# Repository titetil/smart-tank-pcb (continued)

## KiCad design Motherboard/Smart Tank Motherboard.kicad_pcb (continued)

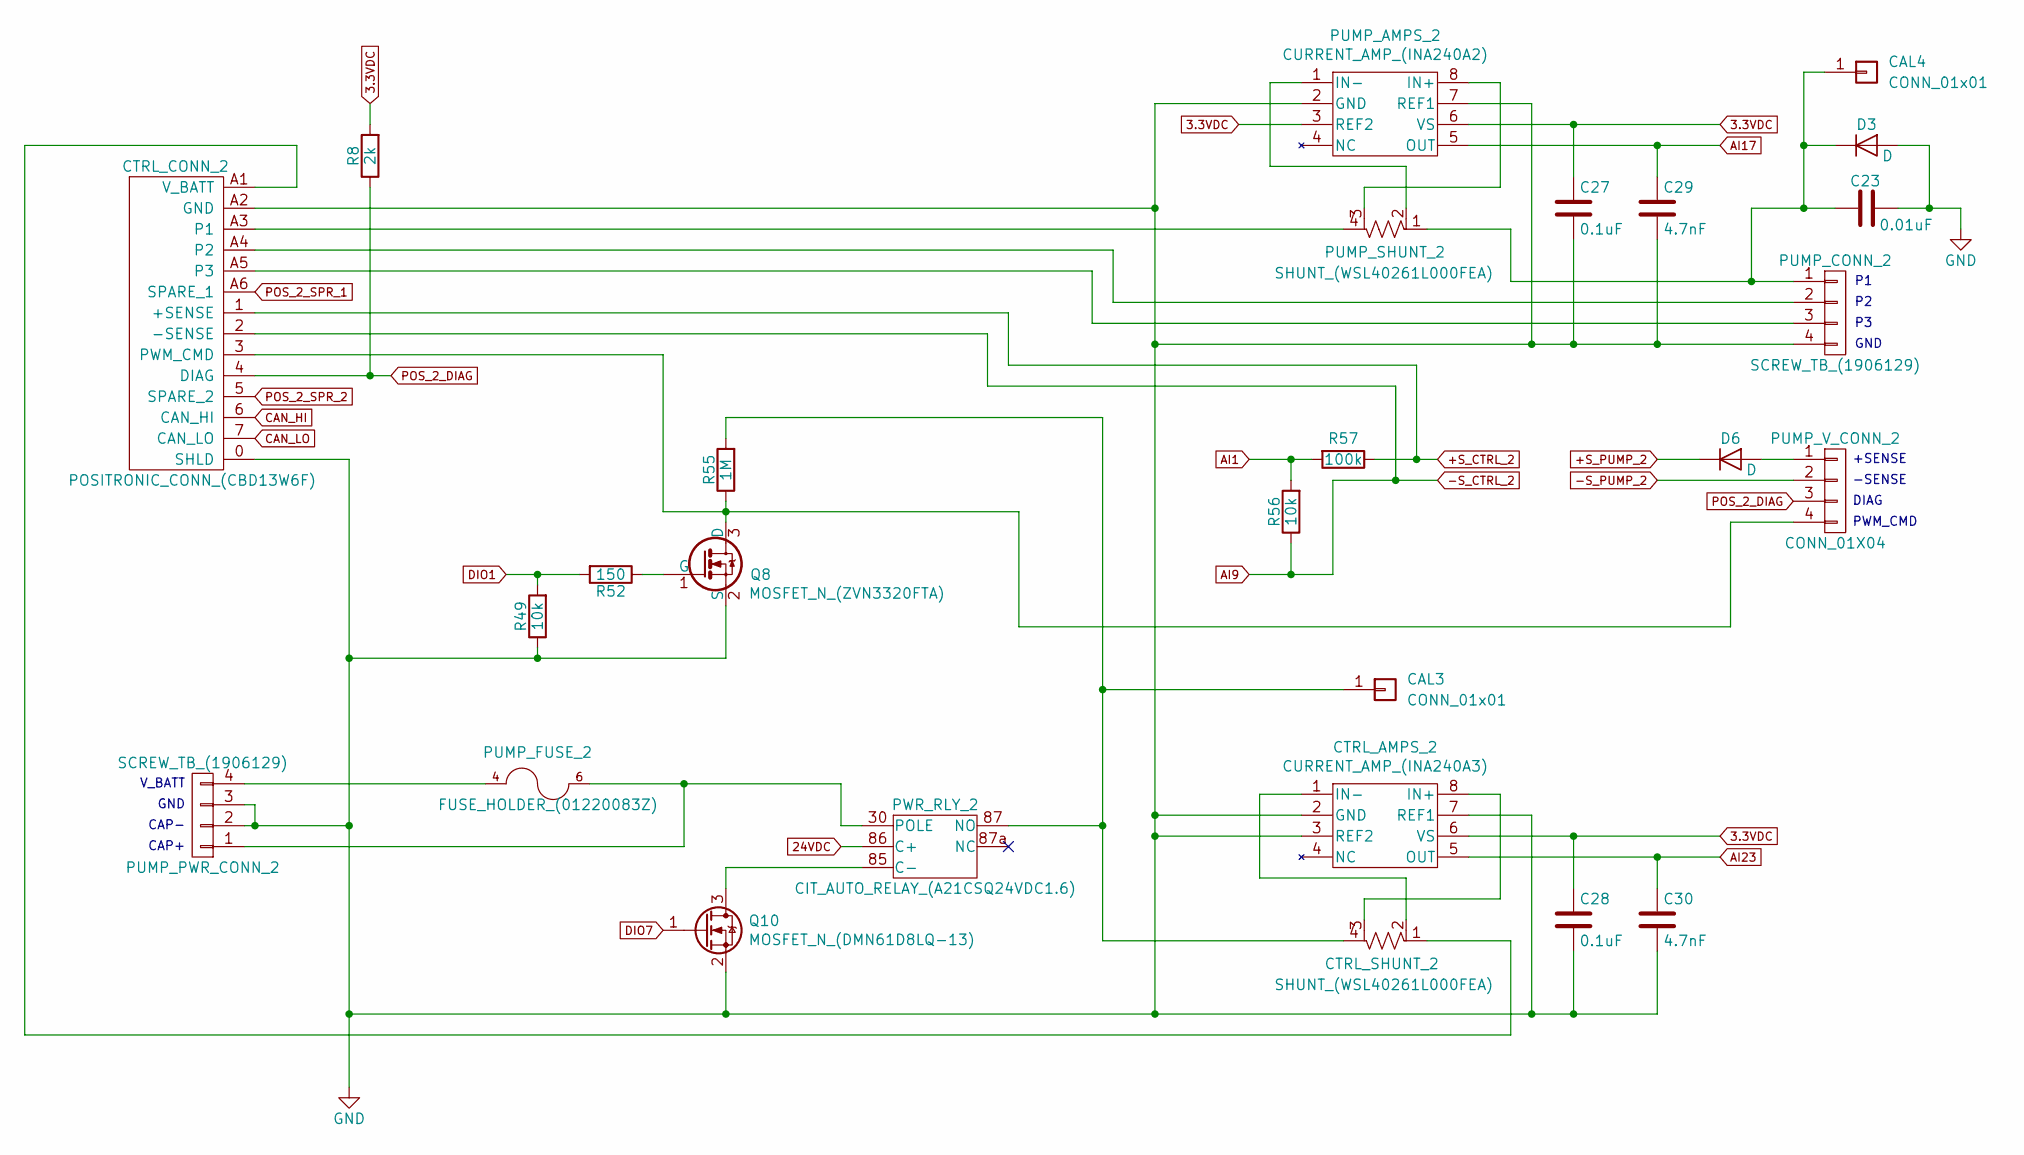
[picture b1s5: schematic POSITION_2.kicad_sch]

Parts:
C23: 0.01uF; C_1206_3216Metric
C27, C28: 0.1uF; C_1206_3216Metric
C29, C30: 4.7nF; C_1206_3216Metric
CAL3, CAL4: CONN_01x01; FEMALE_SPADE_QC_(TE_63969-1)
CTRL_AMPS_2: CURRENT_AMP_(INA240A3); SOIC-8_3.9x4.9mm_P1.27mm
CTRL_CONN_2: POSITRONIC_CONN_(CBD13W6F); POSITRONIC_D-SUB_(CBD13W6F35S600X_AA)
CTRL_SHUNT_2: SHUNT_(WSL40261L000FEA)
D3, D6: D; D_SMA
PUMP_AMPS_2: CURRENT_AMP_(INA240A2); SOIC-8_3.9x4.9mm_P1.27mm
PUMP_CONN_2: SCREW_TB_(1906129); PHNX_TB_SCREW_4_POS_(1906129)
PUMP_FUSE_2: FUSE_HOLDER_(01220083Z)
PUMP_PWR_CONN_2: SCREW_TB_(1906129); PHNX_TB_SCREW_4_POS_(1906129)
PUMP_SHUNT_2: SHUNT_(WSL40261L000FEA)
PUMP_V_CONN_2: CONN_01X04; PHX_TB_HDR_4_POS_STR_(1755752)
PWR_RLY_2: CIT_AUTO_RELAY_(A21CSQ24VDC1.6); TE_AUTO_RELAY_SOCKET_(VCF4-1000)
Q8: MOSFET_N_(ZVN3320FTA); SOT-23
Q10: MOSFET_N_(DMN61D8LQ-13); SOT-23
R8: 2k; R_1206_3216Metric
R49, R56: 10k; R_1206_3216Metric
R52: 150; R_1206_3216Metric
R55: 1M; R_1206_3216Metric
R57: 100k; R_1206_3216Metric

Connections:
3.3VDC: C27.1, C28.1, CTRL_AMPS_2.6 (VS), PUMP_AMPS_2.3 (REF2), PUMP_AMPS_2.6 (VS), R8.2; also elsewhere on the board
24VDC: PWR_RLY_2.86 (C+); also elsewhere on the board
+S_CTRL_2: CTRL_CONN_2.1 (+SENSE), R57.1; also elsewhere on the board
+S_PUMP_2: D6.1 (K); also elsewhere on the board
-S_CTRL_2: CTRL_CONN_2.2 (-SENSE), R56.1; also elsewhere on the board
-S_PUMP_2: PUMP_V_CONN_2.2; also elsewhere on the board
AI1: R56.2, R57.2; also elsewhere on the board
AI17: C29.1, PUMP_AMPS_2.5 (OUT); also elsewhere on the board
AI23: C30.1, CTRL_AMPS_2.5 (OUT); also elsewhere on the board
CAN_HI: CTRL_CONN_2.6 (CAN_HI); also elsewhere on the board
CAN_LO: CTRL_CONN_2.7 (CAN_LO); also elsewhere on the board
DIO1: R49.2, R52.2; also elsewhere on the board
DIO7: Q10.1 (G); also elsewhere on the board
GND: C23.2, C27.2, C28.2, C29.2, C30.2, CTRL_AMPS_2.2 (GND), CTRL_AMPS_2.3 (REF2), CTRL_AMPS_2.7 (REF1), CTRL_CONN_2.0 (SHLD), CTRL_CONN_2.A2 (GND), D3.2 (A), PUMP_AMPS_2.2 (GND), PUMP_AMPS_2.7 (REF1), PUMP_CONN_2.4, PUMP_PWR_CONN_2.2, PUMP_PWR_CONN_2.3, Q8.2 (S), Q10.2 (S), R49.1; also elsewhere on the board
unnamed: CAL3.1, CTRL_SHUNT_2.4, PWR_RLY_2.87 (NO), R55.2
unnamed: C23.1, CAL4.1, D3.1 (K), PUMP_CONN_2.1, PUMP_SHUNT_2.1
unnamed: CTRL_AMPS_2.8 (IN+), CTRL_SHUNT_2.3
unnamed: CTRL_AMPS_2.1 (IN-), CTRL_SHUNT_2.2
unnamed: CTRL_CONN_2.A3 (P1), PUMP_SHUNT_2.4
unnamed: CTRL_CONN_2.A4 (P2), PUMP_CONN_2.2
unnamed: CTRL_CONN_2.A5 (P3), PUMP_CONN_2.3
unnamed: CTRL_CONN_2.3 (PWM_CMD), PUMP_V_CONN_2.4, Q8.3 (D), R55.1
unnamed: CTRL_CONN_2.A1 (V_BATT), CTRL_SHUNT_2.1
unnamed: D6.2 (A), PUMP_V_CONN_2.1
unnamed: PUMP_AMPS_2.8 (IN+), PUMP_SHUNT_2.3
unnamed: PUMP_AMPS_2.1 (IN-), PUMP_SHUNT_2.2
unnamed: PUMP_FUSE_2.6, PUMP_FUSE_2.7, PUMP_PWR_CONN_2.1, PWR_RLY_2.30 (POLE)
unnamed: PUMP_FUSE_2.4, PUMP_FUSE_2.5, PUMP_PWR_CONN_2.4
unnamed: PWR_RLY_2.85 (C-), Q10.3 (D)
unnamed: Q8.1 (G), R52.1
POS_2_DIAG: CTRL_CONN_2.4 (DIAG), PUMP_V_CONN_2.3, R8.1; also elsewhere on the board
POS_2_SPR_1: CTRL_CONN_2.A6 (SPARE_1); also elsewhere on the board
POS_2_SPR_2: CTRL_CONN_2.5 (SPARE_2); also elsewhere on the board

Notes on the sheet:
V_BATT
+SENSE
GND
CAP+
DIAG
GND
-SENSE
PWM_CMD
CAP-

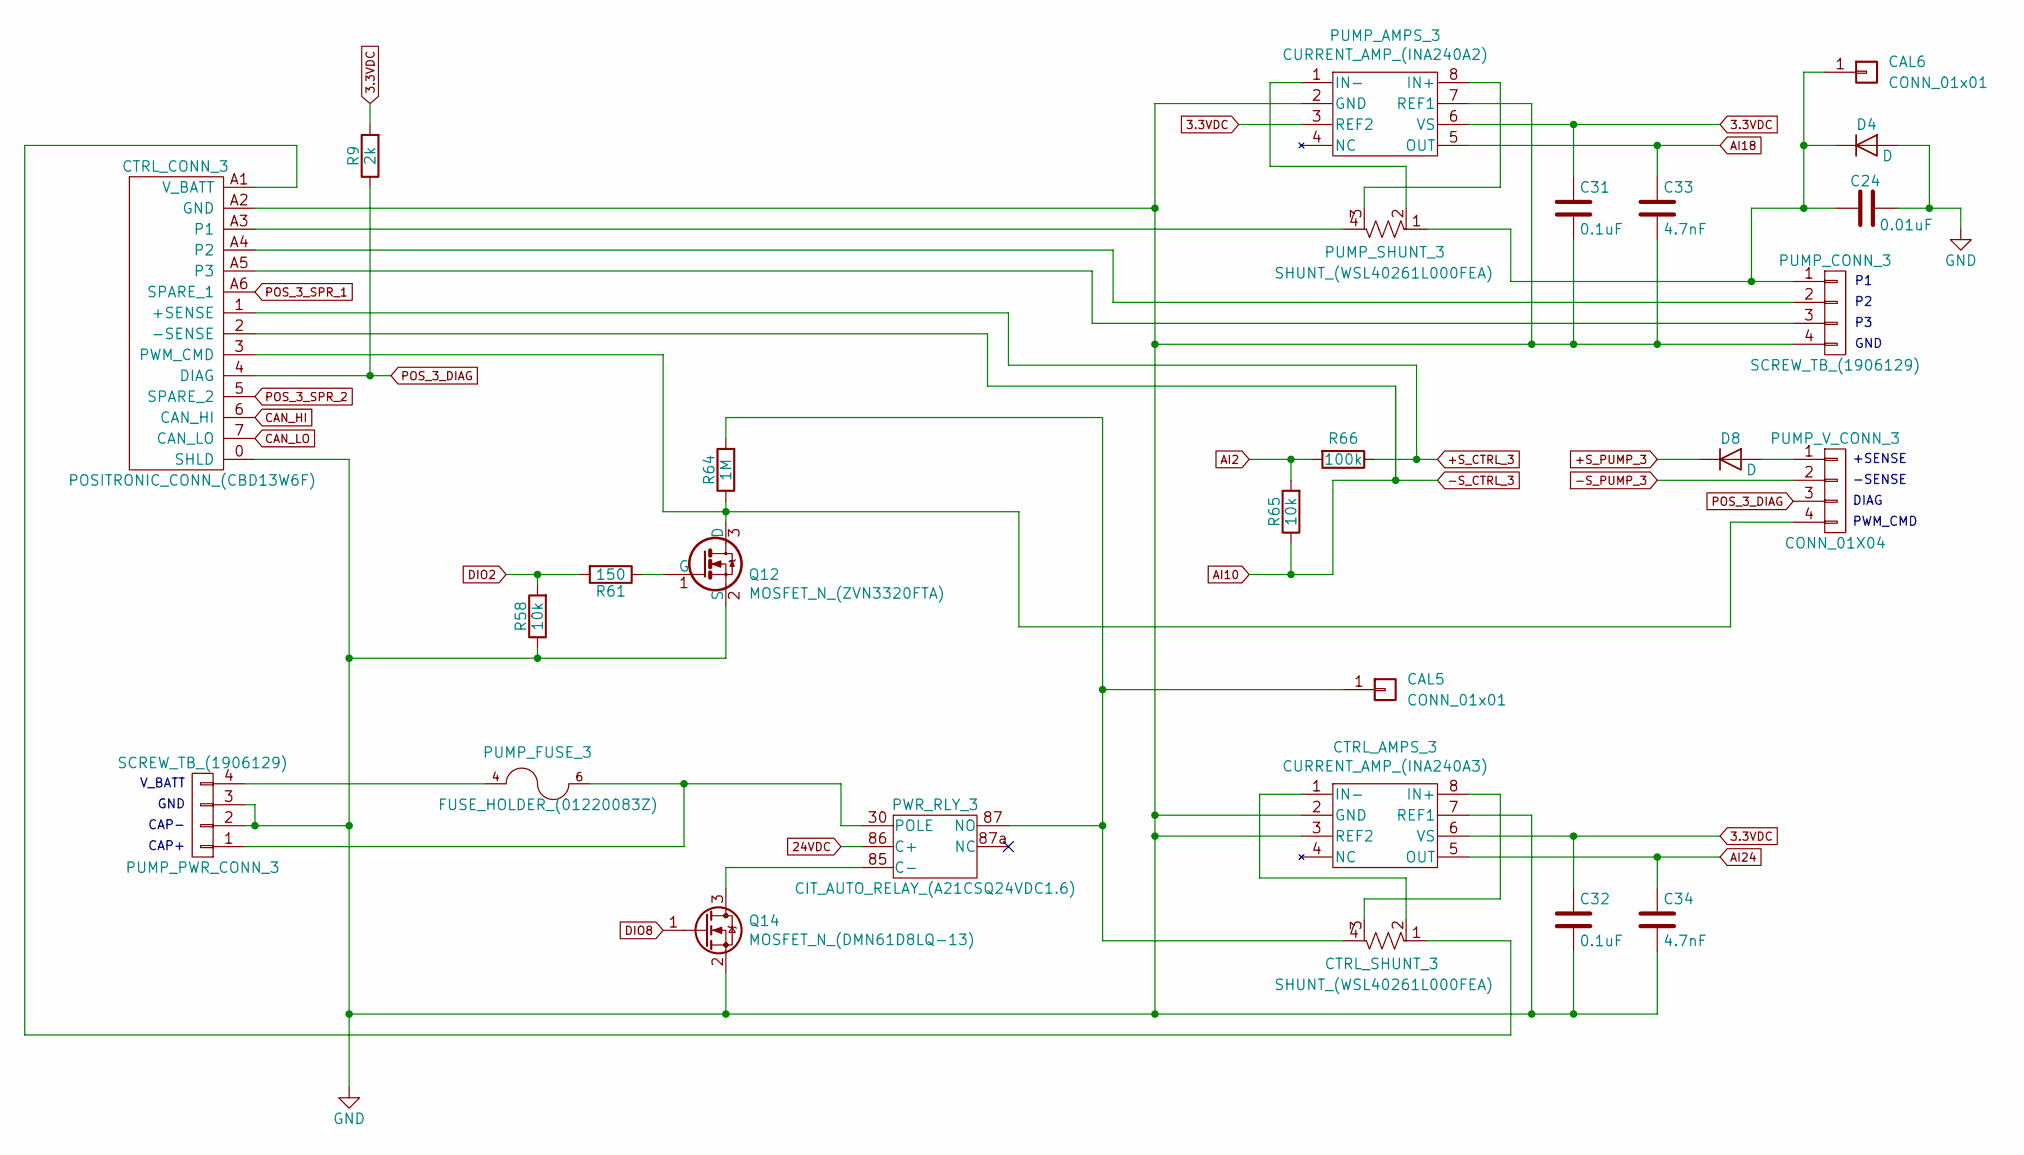
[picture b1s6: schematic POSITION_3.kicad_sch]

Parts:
C24: 0.01uF; C_1206_3216Metric
C31, C32: 0.1uF; C_1206_3216Metric
C33, C34: 4.7nF; C_1206_3216Metric
CAL5, CAL6: CONN_01x01; FEMALE_SPADE_QC_(TE_63969-1)
CTRL_AMPS_3: CURRENT_AMP_(INA240A3); SOIC-8_3.9x4.9mm_P1.27mm
CTRL_CONN_3: POSITRONIC_CONN_(CBD13W6F); POSITRONIC_D-SUB_(CBD13W6F35S600X_AA)
CTRL_SHUNT_3: SHUNT_(WSL40261L000FEA)
D4, D8: D; D_SMA
PUMP_AMPS_3: CURRENT_AMP_(INA240A2); SOIC-8_3.9x4.9mm_P1.27mm
PUMP_CONN_3: SCREW_TB_(1906129); PHNX_TB_SCREW_4_POS_(1906129)
PUMP_FUSE_3: FUSE_HOLDER_(01220083Z)
PUMP_PWR_CONN_3: SCREW_TB_(1906129); PHNX_TB_SCREW_4_POS_(1906129)
PUMP_SHUNT_3: SHUNT_(WSL40261L000FEA)
PUMP_V_CONN_3: CONN_01X04; PHX_TB_HDR_4_POS_STR_(1755752)
PWR_RLY_3: CIT_AUTO_RELAY_(A21CSQ24VDC1.6); TE_AUTO_RELAY_SOCKET_(VCF4-1000)
Q12: MOSFET_N_(ZVN3320FTA); SOT-23
Q14: MOSFET_N_(DMN61D8LQ-13); SOT-23
R9: 2k; R_1206_3216Metric
R58, R65: 10k; R_1206_3216Metric
R61: 150; R_1206_3216Metric
R64: 1M; R_1206_3216Metric
R66: 100k; R_1206_3216Metric

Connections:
3.3VDC: C31.1, C32.1, CTRL_AMPS_3.6 (VS), PUMP_AMPS_3.3 (REF2), PUMP_AMPS_3.6 (VS), R9.2; also elsewhere on the board
24VDC: PWR_RLY_3.86 (C+); also elsewhere on the board
+S_CTRL_3: CTRL_CONN_3.1 (+SENSE), R66.1; also elsewhere on the board
+S_PUMP_3: D8.1 (K); also elsewhere on the board
-S_CTRL_3: CTRL_CONN_3.2 (-SENSE), R65.1; also elsewhere on the board
-S_PUMP_3: PUMP_V_CONN_3.2; also elsewhere on the board
AI2: R65.2, R66.2; also elsewhere on the board
AI18: C33.1, PUMP_AMPS_3.5 (OUT); also elsewhere on the board
AI24: C34.1, CTRL_AMPS_3.5 (OUT); also elsewhere on the board
CAN_HI: CTRL_CONN_3.6 (CAN_HI); also elsewhere on the board
CAN_LO: CTRL_CONN_3.7 (CAN_LO); also elsewhere on the board
DIO2: R58.2, R61.2; also elsewhere on the board
DIO8: Q14.1 (G); also elsewhere on the board
GND: C24.2, C31.2, C32.2, C33.2, C34.2, CTRL_AMPS_3.2 (GND), CTRL_AMPS_3.3 (REF2), CTRL_AMPS_3.7 (REF1), CTRL_CONN_3.0 (SHLD), CTRL_CONN_3.A2 (GND), D4.2 (A), PUMP_AMPS_3.2 (GND), PUMP_AMPS_3.7 (REF1), PUMP_CONN_3.4, PUMP_PWR_CONN_3.2, PUMP_PWR_CONN_3.3, Q12.2 (S), Q14.2 (S), R58.1; also elsewhere on the board
unnamed: CAL5.1, CTRL_SHUNT_3.4, PWR_RLY_3.87 (NO), R64.2
unnamed: C24.1, CAL6.1, D4.1 (K), PUMP_CONN_3.1, PUMP_SHUNT_3.1
unnamed: CTRL_AMPS_3.8 (IN+), CTRL_SHUNT_3.3
unnamed: CTRL_AMPS_3.1 (IN-), CTRL_SHUNT_3.2
unnamed: CTRL_CONN_3.A3 (P1), PUMP_SHUNT_3.4
unnamed: CTRL_CONN_3.A4 (P2), PUMP_CONN_3.2
unnamed: CTRL_CONN_3.A5 (P3), PUMP_CONN_3.3
unnamed: CTRL_CONN_3.3 (PWM_CMD), PUMP_V_CONN_3.4, Q12.3 (D), R64.1
unnamed: CTRL_CONN_3.A1 (V_BATT), CTRL_SHUNT_3.1
unnamed: D8.2 (A), PUMP_V_CONN_3.1
unnamed: PUMP_AMPS_3.8 (IN+), PUMP_SHUNT_3.3
unnamed: PUMP_AMPS_3.1 (IN-), PUMP_SHUNT_3.2
unnamed: PUMP_FUSE_3.6, PUMP_FUSE_3.7, PUMP_PWR_CONN_3.1, PWR_RLY_3.30 (POLE)
unnamed: PUMP_FUSE_3.4, PUMP_FUSE_3.5, PUMP_PWR_CONN_3.4
unnamed: PWR_RLY_3.85 (C-), Q14.3 (D)
unnamed: Q12.1 (G), R61.1
POS_3_DIAG: CTRL_CONN_3.4 (DIAG), PUMP_V_CONN_3.3, R9.1; also elsewhere on the board
POS_3_SPR_1: CTRL_CONN_3.A6 (SPARE_1); also elsewhere on the board
POS_3_SPR_2: CTRL_CONN_3.5 (SPARE_2); also elsewhere on the board

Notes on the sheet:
CAP-
CAP+
-SENSE
V_BATT
PWM_CMD
DIAG
+SENSE
GND
GND

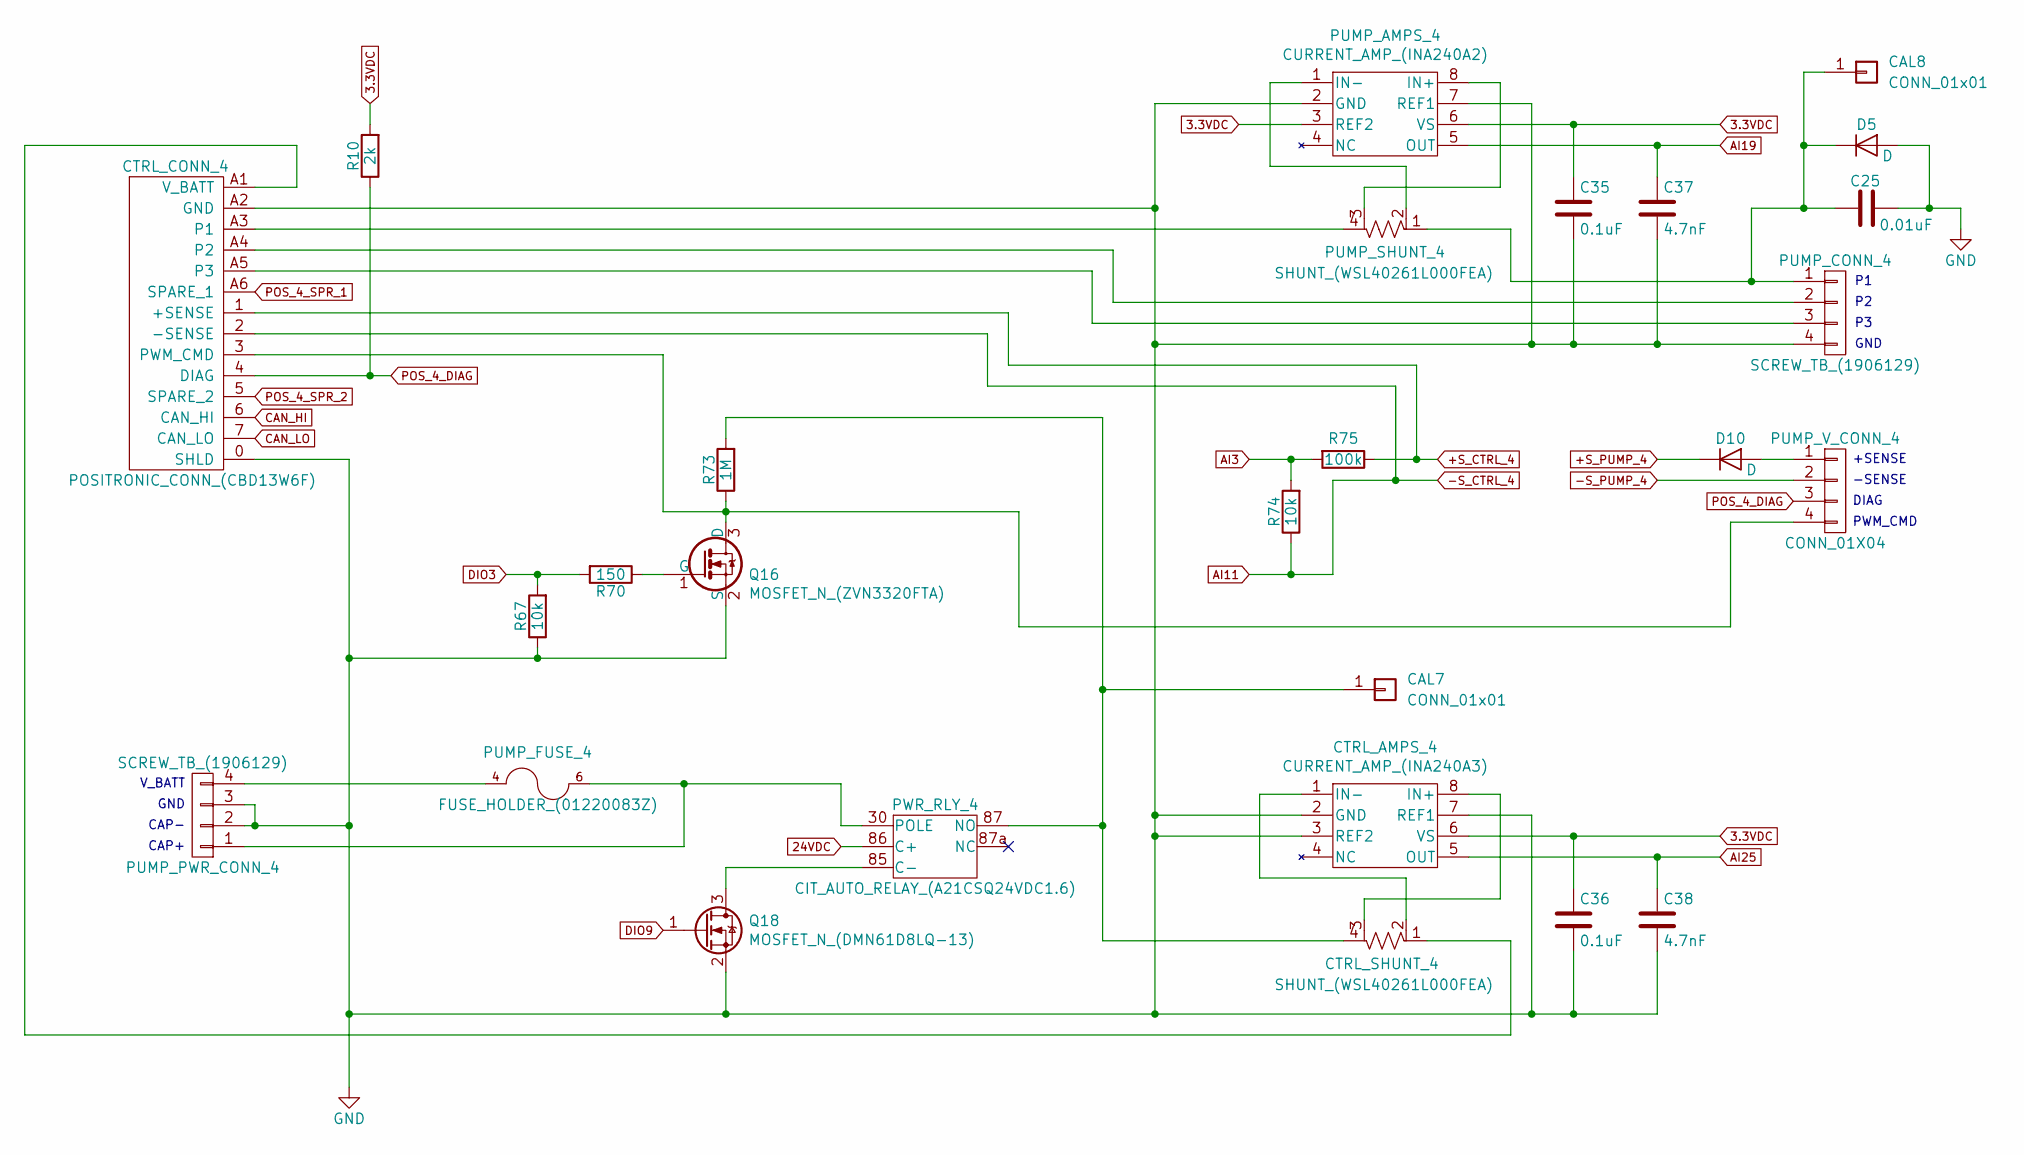
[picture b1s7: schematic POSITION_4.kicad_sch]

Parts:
C25: 0.01uF; C_1206_3216Metric
C35, C36: 0.1uF; C_1206_3216Metric
C37, C38: 4.7nF; C_1206_3216Metric
CAL7, CAL8: CONN_01x01; FEMALE_SPADE_QC_(TE_63969-1)
CTRL_AMPS_4: CURRENT_AMP_(INA240A3); SOIC-8_3.9x4.9mm_P1.27mm
CTRL_CONN_4: POSITRONIC_CONN_(CBD13W6F); POSITRONIC_D-SUB_(CBD13W6F35S600X_AA)
CTRL_SHUNT_4: SHUNT_(WSL40261L000FEA)
D5, D10: D; D_SMA
PUMP_AMPS_4: CURRENT_AMP_(INA240A2); SOIC-8_3.9x4.9mm_P1.27mm
PUMP_CONN_4: SCREW_TB_(1906129); PHNX_TB_SCREW_4_POS_(1906129)
PUMP_FUSE_4: FUSE_HOLDER_(01220083Z)
PUMP_PWR_CONN_4: SCREW_TB_(1906129); PHNX_TB_SCREW_4_POS_(1906129)
PUMP_SHUNT_4: SHUNT_(WSL40261L000FEA)
PUMP_V_CONN_4: CONN_01X04; PHX_TB_HDR_4_POS_STR_(1755752)
PWR_RLY_4: CIT_AUTO_RELAY_(A21CSQ24VDC1.6); TE_AUTO_RELAY_SOCKET_(VCF4-1000)
Q16: MOSFET_N_(ZVN3320FTA); SOT-23
Q18: MOSFET_N_(DMN61D8LQ-13); SOT-23
R10: 2k; R_1206_3216Metric
R67, R74: 10k; R_1206_3216Metric
R70: 150; R_1206_3216Metric
R73: 1M; R_1206_3216Metric
R75: 100k; R_1206_3216Metric

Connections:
3.3VDC: C35.1, C36.1, CTRL_AMPS_4.6 (VS), PUMP_AMPS_4.3 (REF2), PUMP_AMPS_4.6 (VS), R10.2; also elsewhere on the board
24VDC: PWR_RLY_4.86 (C+); also elsewhere on the board
+S_CTRL_4: CTRL_CONN_4.1 (+SENSE), R75.1; also elsewhere on the board
+S_PUMP_4: D10.1 (K); also elsewhere on the board
-S_CTRL_4: CTRL_CONN_4.2 (-SENSE), R74.1; also elsewhere on the board
-S_PUMP_4: PUMP_V_CONN_4.2; also elsewhere on the board
AI3: R74.2, R75.2; also elsewhere on the board
AI19: C37.1, PUMP_AMPS_4.5 (OUT); also elsewhere on the board
AI25: C38.1, CTRL_AMPS_4.5 (OUT); also elsewhere on the board
CAN_HI: CTRL_CONN_4.6 (CAN_HI); also elsewhere on the board
CAN_LO: CTRL_CONN_4.7 (CAN_LO); also elsewhere on the board
DIO3: R67.2, R70.2; also elsewhere on the board
DIO9: Q18.1 (G); also elsewhere on the board
GND: C25.2, C35.2, C36.2, C37.2, C38.2, CTRL_AMPS_4.2 (GND), CTRL_AMPS_4.3 (REF2), CTRL_AMPS_4.7 (REF1), CTRL_CONN_4.0 (SHLD), CTRL_CONN_4.A2 (GND), D5.2 (A), PUMP_AMPS_4.2 (GND), PUMP_AMPS_4.7 (REF1), PUMP_CONN_4.4, PUMP_PWR_CONN_4.2, PUMP_PWR_CONN_4.3, Q16.2 (S), Q18.2 (S), R67.1; also elsewhere on the board
unnamed: CAL7.1, CTRL_SHUNT_4.4, PWR_RLY_4.87 (NO), R73.2
unnamed: C25.1, CAL8.1, D5.1 (K), PUMP_CONN_4.1, PUMP_SHUNT_4.1
unnamed: CTRL_AMPS_4.8 (IN+), CTRL_SHUNT_4.3
unnamed: CTRL_AMPS_4.1 (IN-), CTRL_SHUNT_4.2
unnamed: CTRL_CONN_4.A3 (P1), PUMP_SHUNT_4.4
unnamed: CTRL_CONN_4.A4 (P2), PUMP_CONN_4.2
unnamed: CTRL_CONN_4.A5 (P3), PUMP_CONN_4.3
unnamed: CTRL_CONN_4.3 (PWM_CMD), PUMP_V_CONN_4.4, Q16.3 (D), R73.1
unnamed: CTRL_CONN_4.A1 (V_BATT), CTRL_SHUNT_4.1
unnamed: D10.2 (A), PUMP_V_CONN_4.1
unnamed: PUMP_AMPS_4.8 (IN+), PUMP_SHUNT_4.3
unnamed: PUMP_AMPS_4.1 (IN-), PUMP_SHUNT_4.2
unnamed: PUMP_FUSE_4.6, PUMP_FUSE_4.7, PUMP_PWR_CONN_4.1, PWR_RLY_4.30 (POLE)
unnamed: PUMP_FUSE_4.4, PUMP_FUSE_4.5, PUMP_PWR_CONN_4.4
unnamed: PWR_RLY_4.85 (C-), Q18.3 (D)
unnamed: Q16.1 (G), R70.1
POS_4_DIAG: CTRL_CONN_4.4 (DIAG), PUMP_V_CONN_4.3, R10.1; also elsewhere on the board
POS_4_SPR_1: CTRL_CONN_4.A6 (SPARE_1); also elsewhere on the board
POS_4_SPR_2: CTRL_CONN_4.5 (SPARE_2); also elsewhere on the board

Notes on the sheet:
PWM_CMD
CAP-
DIAG
CAP+
GND
GND
V_BATT
-SENSE
+SENSE

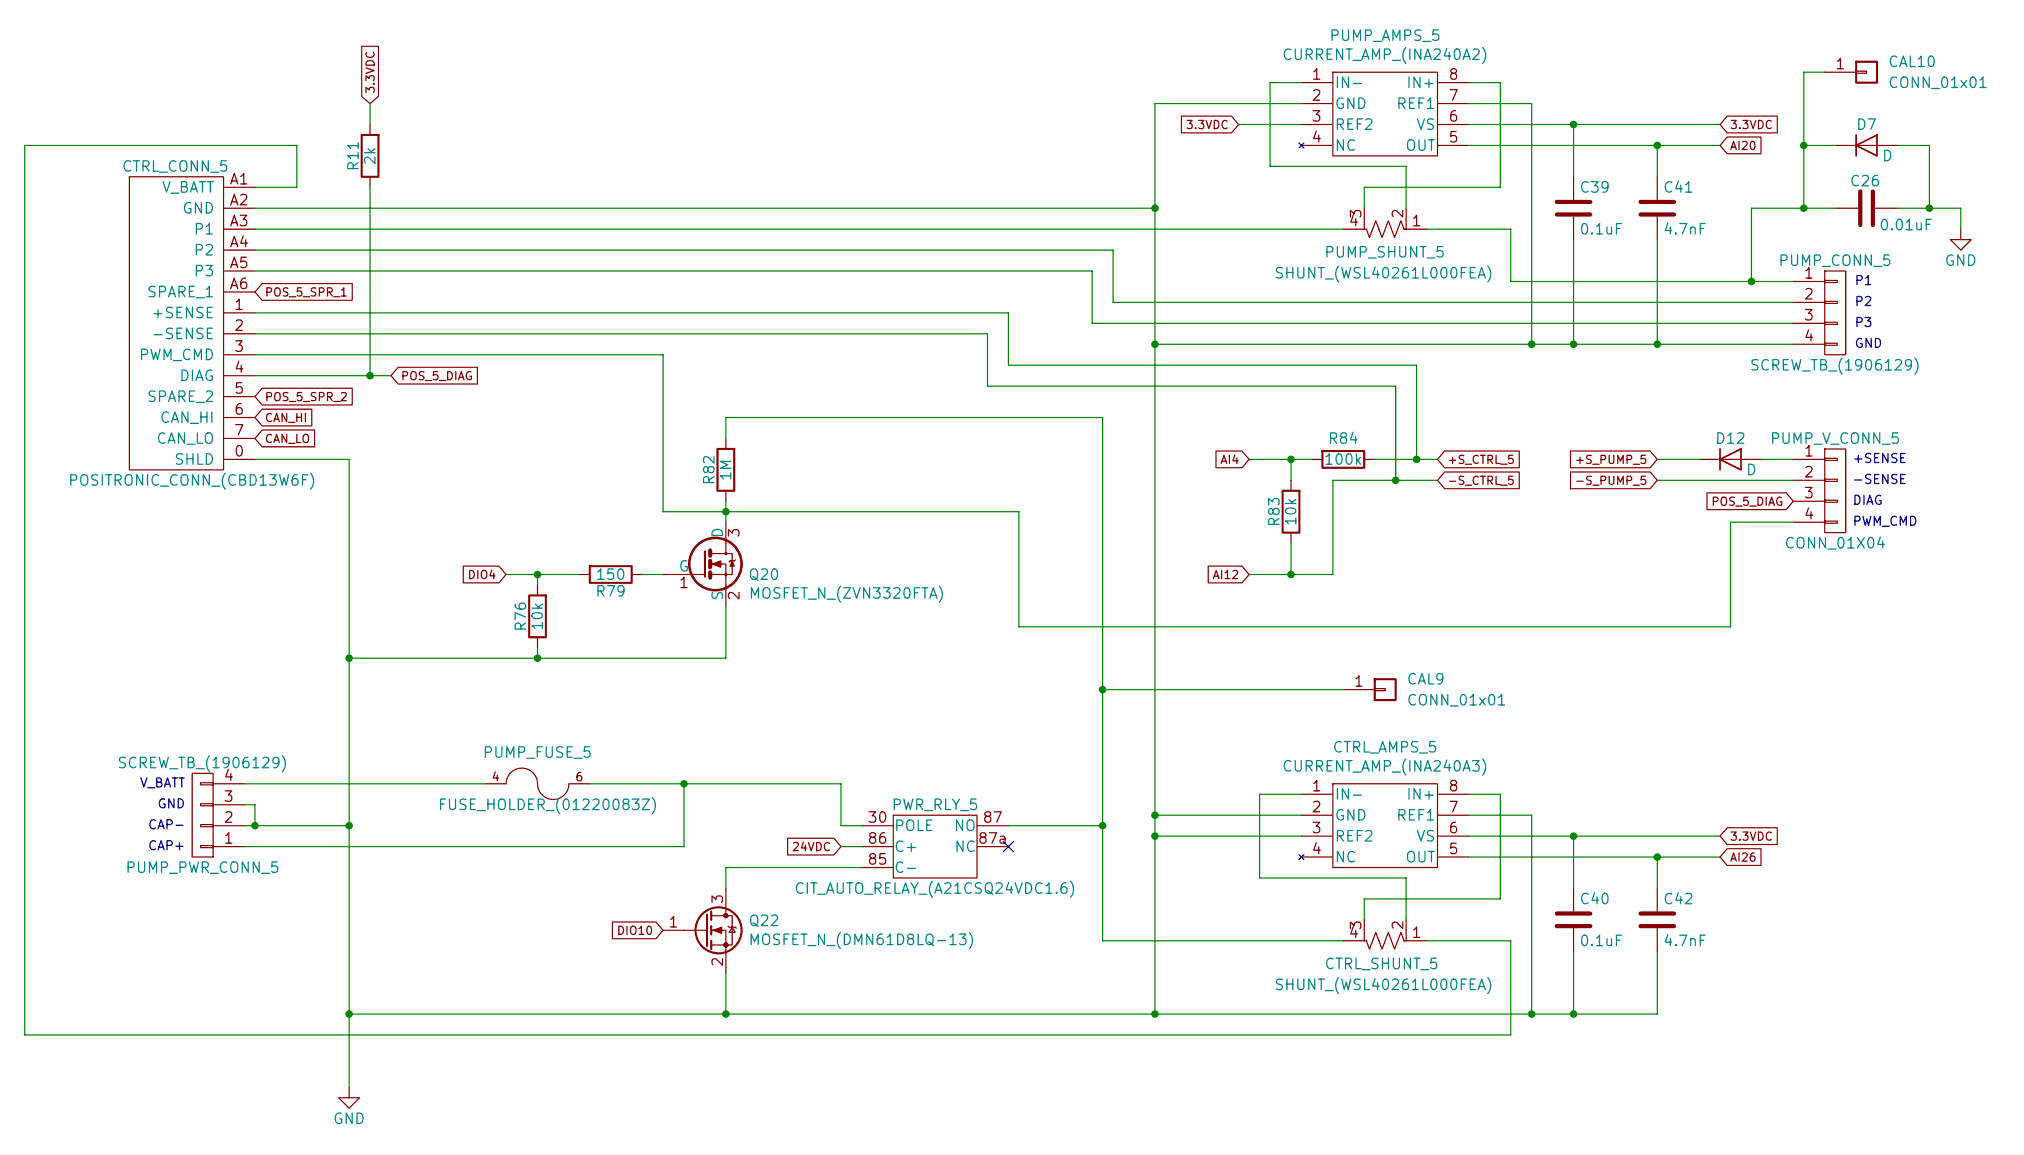
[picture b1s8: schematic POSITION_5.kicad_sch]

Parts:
C26: 0.01uF; C_1206_3216Metric
C39, C40: 0.1uF; C_1206_3216Metric
C41, C42: 4.7nF; C_1206_3216Metric
CAL9, CAL10: CONN_01x01; FEMALE_SPADE_QC_(TE_63969-1)
CTRL_AMPS_5: CURRENT_AMP_(INA240A3); SOIC-8_3.9x4.9mm_P1.27mm
CTRL_CONN_5: POSITRONIC_CONN_(CBD13W6F); POSITRONIC_D-SUB_(CBD13W6F35S600X_AA)
CTRL_SHUNT_5: SHUNT_(WSL40261L000FEA)
D7, D12: D; D_SMA
PUMP_AMPS_5: CURRENT_AMP_(INA240A2); SOIC-8_3.9x4.9mm_P1.27mm
PUMP_CONN_5: SCREW_TB_(1906129); PHNX_TB_SCREW_4_POS_(1906129)
PUMP_FUSE_5: FUSE_HOLDER_(01220083Z)
PUMP_PWR_CONN_5: SCREW_TB_(1906129); PHNX_TB_SCREW_4_POS_(1906129)
PUMP_SHUNT_5: SHUNT_(WSL40261L000FEA)
PUMP_V_CONN_5: CONN_01X04; PHX_TB_HDR_4_POS_STR_(1755752)
PWR_RLY_5: CIT_AUTO_RELAY_(A21CSQ24VDC1.6); TE_AUTO_RELAY_SOCKET_(VCF4-1000)
Q20: MOSFET_N_(ZVN3320FTA); SOT-23
Q22: MOSFET_N_(DMN61D8LQ-13); SOT-23
R11: 2k; R_1206_3216Metric
R76, R83: 10k; R_1206_3216Metric
R79: 150; R_1206_3216Metric
R82: 1M; R_1206_3216Metric
R84: 100k; R_1206_3216Metric

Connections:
3.3VDC: C39.1, C40.1, CTRL_AMPS_5.6 (VS), PUMP_AMPS_5.3 (REF2), PUMP_AMPS_5.6 (VS), R11.2; also elsewhere on the board
24VDC: PWR_RLY_5.86 (C+); also elsewhere on the board
+S_CTRL_5: CTRL_CONN_5.1 (+SENSE), R84.1; also elsewhere on the board
+S_PUMP_5: D12.1 (K); also elsewhere on the board
-S_CTRL_5: CTRL_CONN_5.2 (-SENSE), R83.1; also elsewhere on the board
-S_PUMP_5: PUMP_V_CONN_5.2; also elsewhere on the board
AI4: R83.2, R84.2; also elsewhere on the board
AI20: C41.1, PUMP_AMPS_5.5 (OUT); also elsewhere on the board
AI26: C42.1, CTRL_AMPS_5.5 (OUT); also elsewhere on the board
CAN_HI: CTRL_CONN_5.6 (CAN_HI); also elsewhere on the board
CAN_LO: CTRL_CONN_5.7 (CAN_LO); also elsewhere on the board
DIO4: R76.2, R79.2; also elsewhere on the board
DIO10: Q22.1 (G); also elsewhere on the board
GND: C26.2, C39.2, C40.2, C41.2, C42.2, CTRL_AMPS_5.2 (GND), CTRL_AMPS_5.3 (REF2), CTRL_AMPS_5.7 (REF1), CTRL_CONN_5.0 (SHLD), CTRL_CONN_5.A2 (GND), D7.2 (A), PUMP_AMPS_5.2 (GND), PUMP_AMPS_5.7 (REF1), PUMP_CONN_5.4, PUMP_PWR_CONN_5.2, PUMP_PWR_CONN_5.3, Q20.2 (S), Q22.2 (S), R76.1; also elsewhere on the board
unnamed: CAL9.1, CTRL_SHUNT_5.4, PWR_RLY_5.87 (NO), R82.2
unnamed: C26.1, CAL10.1, D7.1 (K), PUMP_CONN_5.1, PUMP_SHUNT_5.1
unnamed: CTRL_AMPS_5.8 (IN+), CTRL_SHUNT_5.3
unnamed: CTRL_AMPS_5.1 (IN-), CTRL_SHUNT_5.2
unnamed: CTRL_CONN_5.A3 (P1), PUMP_SHUNT_5.4
unnamed: CTRL_CONN_5.A4 (P2), PUMP_CONN_5.2
unnamed: CTRL_CONN_5.A5 (P3), PUMP_CONN_5.3
unnamed: CTRL_CONN_5.3 (PWM_CMD), PUMP_V_CONN_5.4, Q20.3 (D), R82.1
unnamed: CTRL_CONN_5.A1 (V_BATT), CTRL_SHUNT_5.1
unnamed: D12.2 (A), PUMP_V_CONN_5.1
unnamed: PUMP_AMPS_5.8 (IN+), PUMP_SHUNT_5.3
unnamed: PUMP_AMPS_5.1 (IN-), PUMP_SHUNT_5.2
unnamed: PUMP_FUSE_5.6, PUMP_FUSE_5.7, PUMP_PWR_CONN_5.1, PWR_RLY_5.30 (POLE)
unnamed: PUMP_FUSE_5.4, PUMP_FUSE_5.5, PUMP_PWR_CONN_5.4
unnamed: PWR_RLY_5.85 (C-), Q22.3 (D)
unnamed: Q20.1 (G), R79.1
POS_5_DIAG: CTRL_CONN_5.4 (DIAG), PUMP_V_CONN_5.3, R11.1; also elsewhere on the board
POS_5_SPR_1: CTRL_CONN_5.A6 (SPARE_1); also elsewhere on the board
POS_5_SPR_2: CTRL_CONN_5.5 (SPARE_2); also elsewhere on the board

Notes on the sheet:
GND
PWM_CMD
-SENSE
V_BATT
GND
CAP-
CAP+
DIAG
+SENSE

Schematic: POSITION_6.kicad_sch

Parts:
C17: 0.01uF; C_1206_3216Metric
C43, C44: 0.1uF; C_1206_3216Metric
C45, C46: 4.7nF; C_1206_3216Metric
CAL11, CAL12: CONN_01x01; FEMALE_SPADE_QC_(TE_63969-1)
CTRL_AMPS_6: CURRENT_AMP_(INA240A3); SOIC-8_3.9x4.9mm_P1.27mm
CTRL_CONN_6: POSITRONIC_CONN_(CBD13W6F); POSITRONIC_D-SUB_(CBD13W6F35S600X_AA)
CTRL_SHUNT_6: SHUNT_(WSL40261L000FEA)
D9, D14: D; D_SMA
PUMP_AMPS_6: CURRENT_AMP_(INA240A2); SOIC-8_3.9x4.9mm_P1.27mm
PUMP_CONN_6: SCREW_TB_(1906129); PHNX_TB_SCREW_4_POS_(1906129)
PUMP_FUSE_6: FUSE_HOLDER_(01220083Z)
PUMP_PWR_CONN_6: SCREW_TB_(1906129); PHNX_TB_SCREW_4_POS_(1906129)
PUMP_SHUNT_6: SHUNT_(WSL40261L000FEA)
PUMP_V_CONN_6: CONN_01X04; PHX_TB_HDR_4_POS_STR_(1755752)
PWR_RLY_6: CIT_AUTO_RELAY_(A21CSQ24VDC1.6); TE_AUTO_RELAY_SOCKET_(VCF4-1000)
Q24: MOSFET_N_(ZVN3320FTA); SOT-23
Q26: MOSFET_N_(DMN61D8LQ-13); SOT-23
R12: 2k; R_1206_3216Metric
R85, R92: 10k; R_1206_3216Metric
R88: 150; R_1206_3216Metric
R91: 1M; R_1206_3216Metric
R93: 100k; R_1206_3216Metric

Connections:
3.3VDC: C43.1, C44.1, CTRL_AMPS_6.6 (VS), PUMP_AMPS_6.3 (REF2), PUMP_AMPS_6.6 (VS), R12.2; also elsewhere on the board
24VDC: PWR_RLY_6.86 (C+); also elsewhere on the board
+S_CTRL_6: CTRL_CONN_6.1 (+SENSE), R93.1; also elsewhere on the board
+S_PUMP_6: D14.1 (K); also elsewhere on the board
-S_CTRL_6: CTRL_CONN_6.2 (-SENSE), R92.1; also elsewhere on the board
-S_PUMP_6: PUMP_V_CONN_6.2; also elsewhere on the board
AI5: R92.2, R93.2; also elsewhere on the board
AI21: C45.1, PUMP_AMPS_6.5 (OUT); also elsewhere on the board
AI27: C46.1, CTRL_AMPS_6.5 (OUT); also elsewhere on the board
CAN_HI: CTRL_CONN_6.6 (CAN_HI); also elsewhere on the board
CAN_LO: CTRL_CONN_6.7 (CAN_LO); also elsewhere on the board
DIO5: R85.2, R88.2; also elsewhere on the board
DIO11: Q26.1 (G); also elsewhere on the board
GND: C17.2, C43.2, C44.2, C45.2, C46.2, CTRL_AMPS_6.2 (GND), CTRL_AMPS_6.3 (REF2), CTRL_AMPS_6.7 (REF1), CTRL_CONN_6.0 (SHLD), CTRL_CONN_6.A2 (GND), D9.2 (A), PUMP_AMPS_6.2 (GND), PUMP_AMPS_6.7 (REF1), PUMP_CONN_6.4, PUMP_PWR_CONN_6.2, PUMP_PWR_CONN_6.3, Q24.2 (S), Q26.2 (S), R85.1; also elsewhere on the board
unnamed: CAL11.1, CTRL_SHUNT_6.4, PWR_RLY_6.87 (NO), R91.2
unnamed: C17.1, CAL12.1, D9.1 (K), PUMP_CONN_6.1, PUMP_SHUNT_6.1
unnamed: CTRL_AMPS_6.8 (IN+), CTRL_SHUNT_6.3
unnamed: CTRL_AMPS_6.1 (IN-), CTRL_SHUNT_6.2
unnamed: CTRL_CONN_6.A3 (P1), PUMP_SHUNT_6.4
unnamed: CTRL_CONN_6.A4 (P2), PUMP_CONN_6.2
unnamed: CTRL_CONN_6.A5 (P3), PUMP_CONN_6.3
unnamed: CTRL_CONN_6.3 (PWM_CMD), PUMP_V_CONN_6.4, Q24.3 (D), R91.1
unnamed: CTRL_CONN_6.A1 (V_BATT), CTRL_SHUNT_6.1
unnamed: D14.2 (A), PUMP_V_CONN_6.1
unnamed: PUMP_AMPS_6.8 (IN+), PUMP_SHUNT_6.3
unnamed: PUMP_AMPS_6.1 (IN-), PUMP_SHUNT_6.2
unnamed: PUMP_FUSE_6.6, PUMP_FUSE_6.7, PUMP_PWR_CONN_6.1, PWR_RLY_6.30 (POLE)
unnamed: PUMP_FUSE_6.4, PUMP_FUSE_6.5, PUMP_PWR_CONN_6.4
unnamed: PWR_RLY_6.85 (C-), Q26.3 (D)
unnamed: Q24.1 (G), R88.1
POS_6_DIAG: CTRL_CONN_6.4 (DIAG), PUMP_V_CONN_6.3, R12.1; also elsewhere on the board
POS_6_SPR_1: CTRL_CONN_6.A6 (SPARE_1); also elsewhere on the board
POS_6_SPR_2: CTRL_CONN_6.5 (SPARE_2); also elsewhere on the board

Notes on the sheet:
DIAG
GND
CAP-
+SENSE
CAP+
-SENSE
PWM_CMD
GND
V_BATT

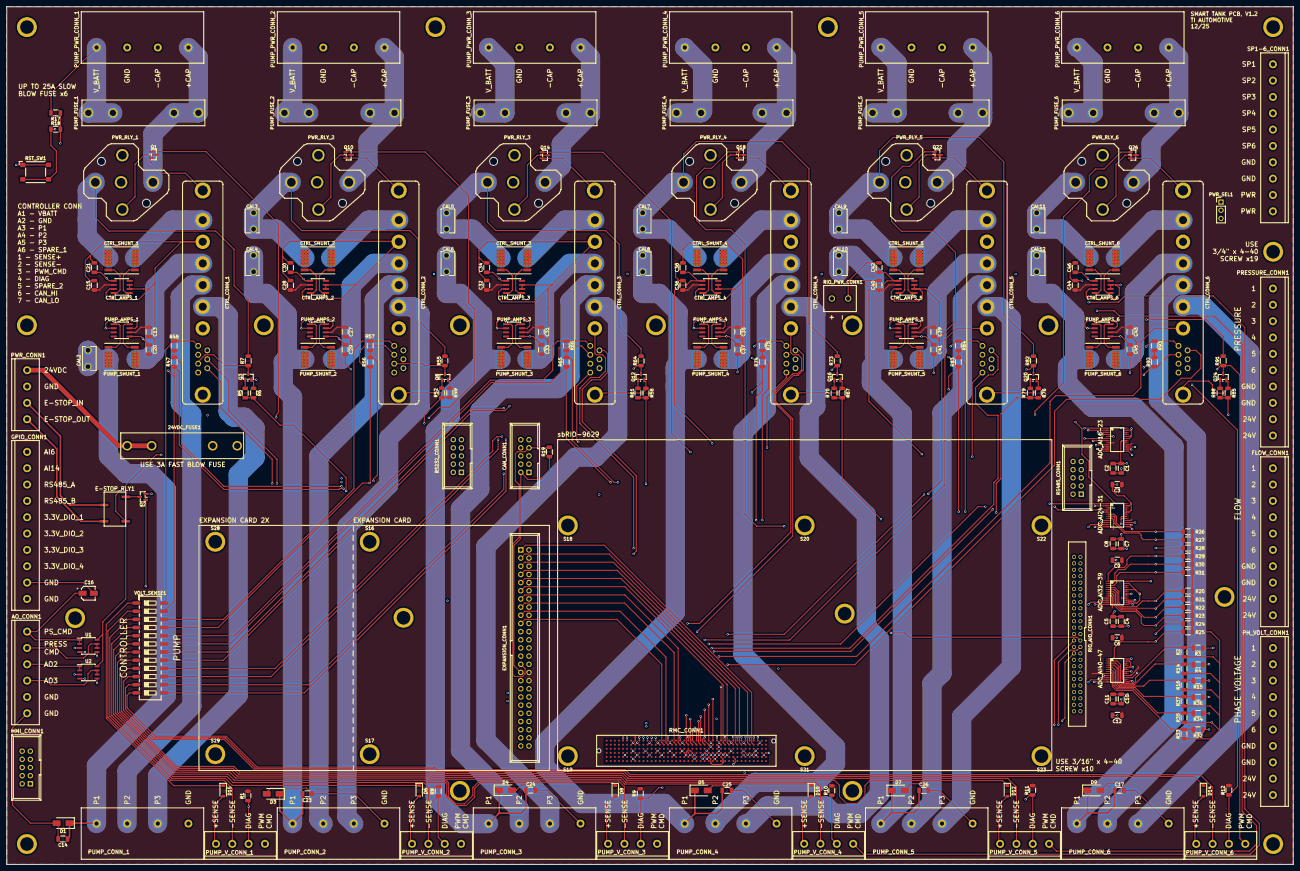
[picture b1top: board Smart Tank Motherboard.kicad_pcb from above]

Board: 10 copper layers, 400.1 x 266.7 mm, 257 parts (0 on the bottom side), 267 nets.

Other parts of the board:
S1, S2, S3, S4, S5, S6, S7, S8, S9, S10, S11, S12, S13, S14, S15, S24, S25, S26, S27: PEM_STANDOFF_THRU_(SMTSOB-116-12ET)
S16, S17, S18, S19, S20, S21, S22, S23, S28, S29: MountingHole_3.2mm_M3; PEM_STANDOFF_4-40_(SMTSOB-440-12ET)

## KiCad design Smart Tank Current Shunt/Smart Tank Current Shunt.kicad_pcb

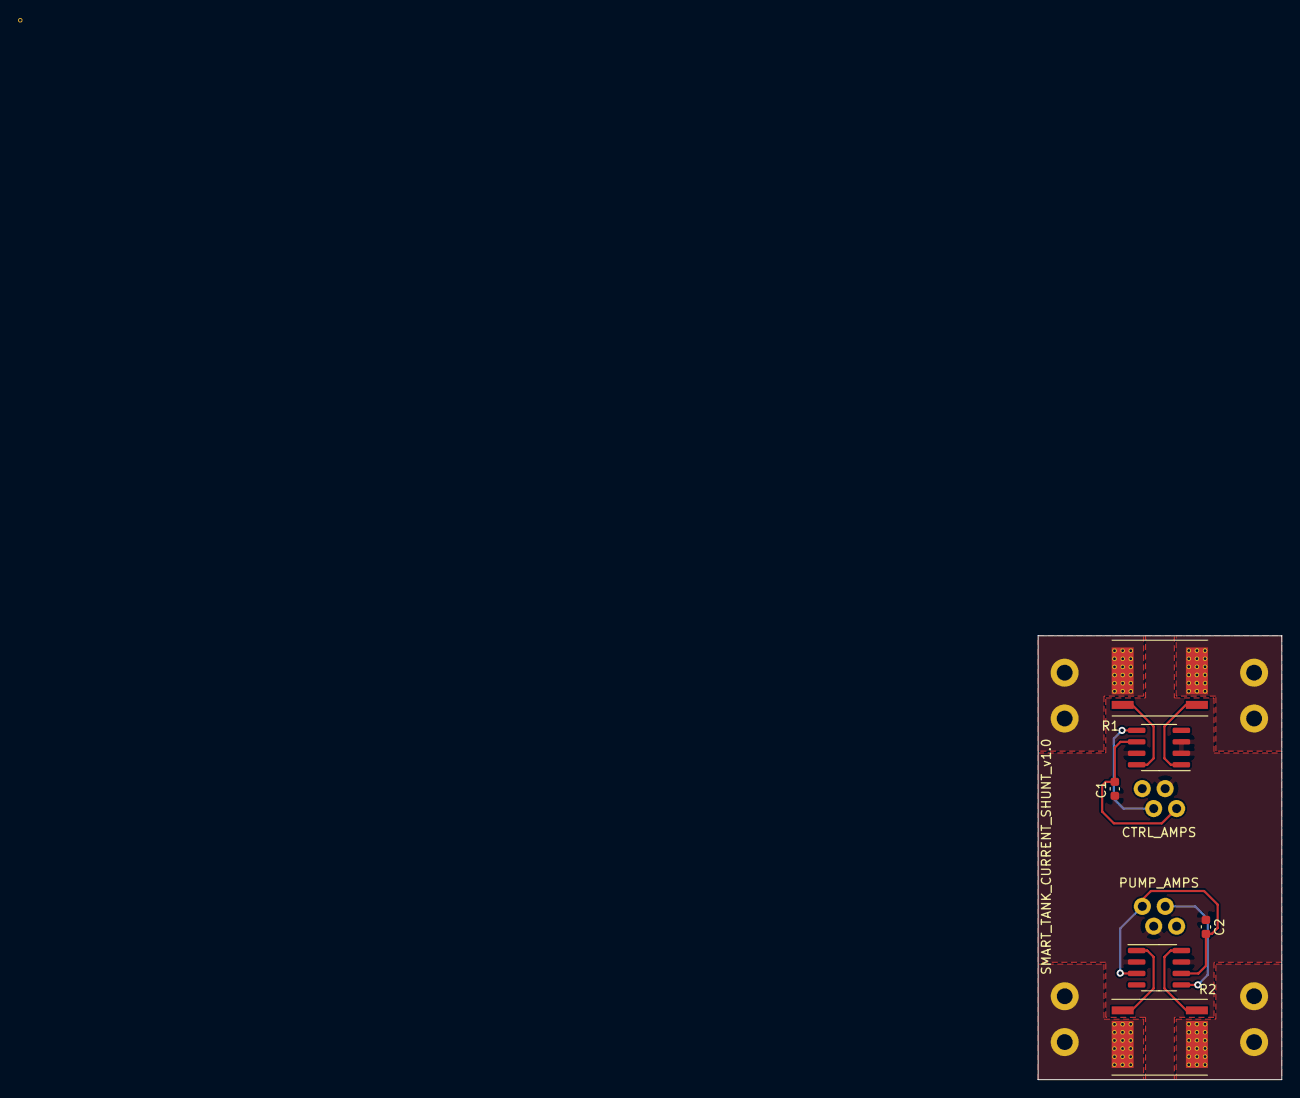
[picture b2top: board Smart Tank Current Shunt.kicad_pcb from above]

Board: 6 copper layers, 27.0 x 49.2 mm, 7 parts (0 on the bottom side), 13 nets.

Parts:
C1, C2: 0.1uF; C_0603_1608Metric
CTRL_AMPS: CURRENT_AMP_(INA240A3); SOIC-8_3.9x4.9mm_P1.27mm
J1: CURRENT_SHUNT_INTERFACE; SMART_TANK_SHUNT_INTERFACE
PUMP_AMPS: CURRENT_AMP_(INA240A3); SOIC-8_3.9x4.9mm_P1.27mm
R1, R2: SHUNT_(WSL40261L000FEA)

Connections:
Earth: C1.2, C2.2, CTRL_AMPS.2, CTRL_AMPS.3, CTRL_AMPS.7, J1.5, J1.11, PUMP_AMPS.2, PUMP_AMPS.7
unnamed: C1.1, CTRL_AMPS.6, J1.6
unnamed: C2.1, J1.12, PUMP_AMPS.3, PUMP_AMPS.6
unnamed: CTRL_AMPS.1, R1.2
unnamed: CTRL_AMPS.5, J1.4
unnamed: CTRL_AMPS.8, R1.3
unnamed: J1.1, R1.4
unnamed: J1.2, R1.1
unnamed: J1.7, R2.4
unnamed: J1.8, R2.1
unnamed: J1.10, PUMP_AMPS.5
unnamed: PUMP_AMPS.1, R2.2
unnamed: PUMP_AMPS.8, R2.3
